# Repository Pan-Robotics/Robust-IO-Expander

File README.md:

# Robust-IO-Expander

    1. Dual MCP23S17 ICs: Harness the power of two MCP23S17 16-Bit I/O Expander ICs – one dedicated for inputs, ensuring robust data acquisition, 
    and the other exclusively for outputs, enabling precise device control.
    
    2. Galvanic Isolation with Opto Switches: Prioritize safety in your projects. Our I/O Expansion Module integrates opto switches for galvanic isolation, 
    shielding your electronics from voltage spikes and surges, ensuring secure and reliable operation.
    
    3. SPI Interface: Interact effortlessly with your system via the SPI interface. This streamlined communication protocol ensures swift and efficient data exchange, 
    allowing you to focus on the heart of your project.
    
    4. Connector Options: Tailor the module to your needs. Choose between 2.54mm header connectors for easy integration into your existing setups or Push terminals for a robust, secure connection. 
    The choice is yours, ensuring seamless compatibility with your specific project requirements.
    
    5. Effortless Expansion: Need more I/O pins? No problem! Our module is stackable, facilitating seamless expansion. 
    Connect multiple modules effortlessly to scale your projects without limitations, providing endless opportunities for your creative endeavors.
    
    6. Unparalleled Flexibility: Whether you're orchestrating automation systems, developing cutting-edge robotics, or creating interactive art installations, 
    the versatility of our I/O Expansion Module amplifies your creativity. Control motors, sensors, LEDs, and various devices effortlessly, opening doors to innovative projects.

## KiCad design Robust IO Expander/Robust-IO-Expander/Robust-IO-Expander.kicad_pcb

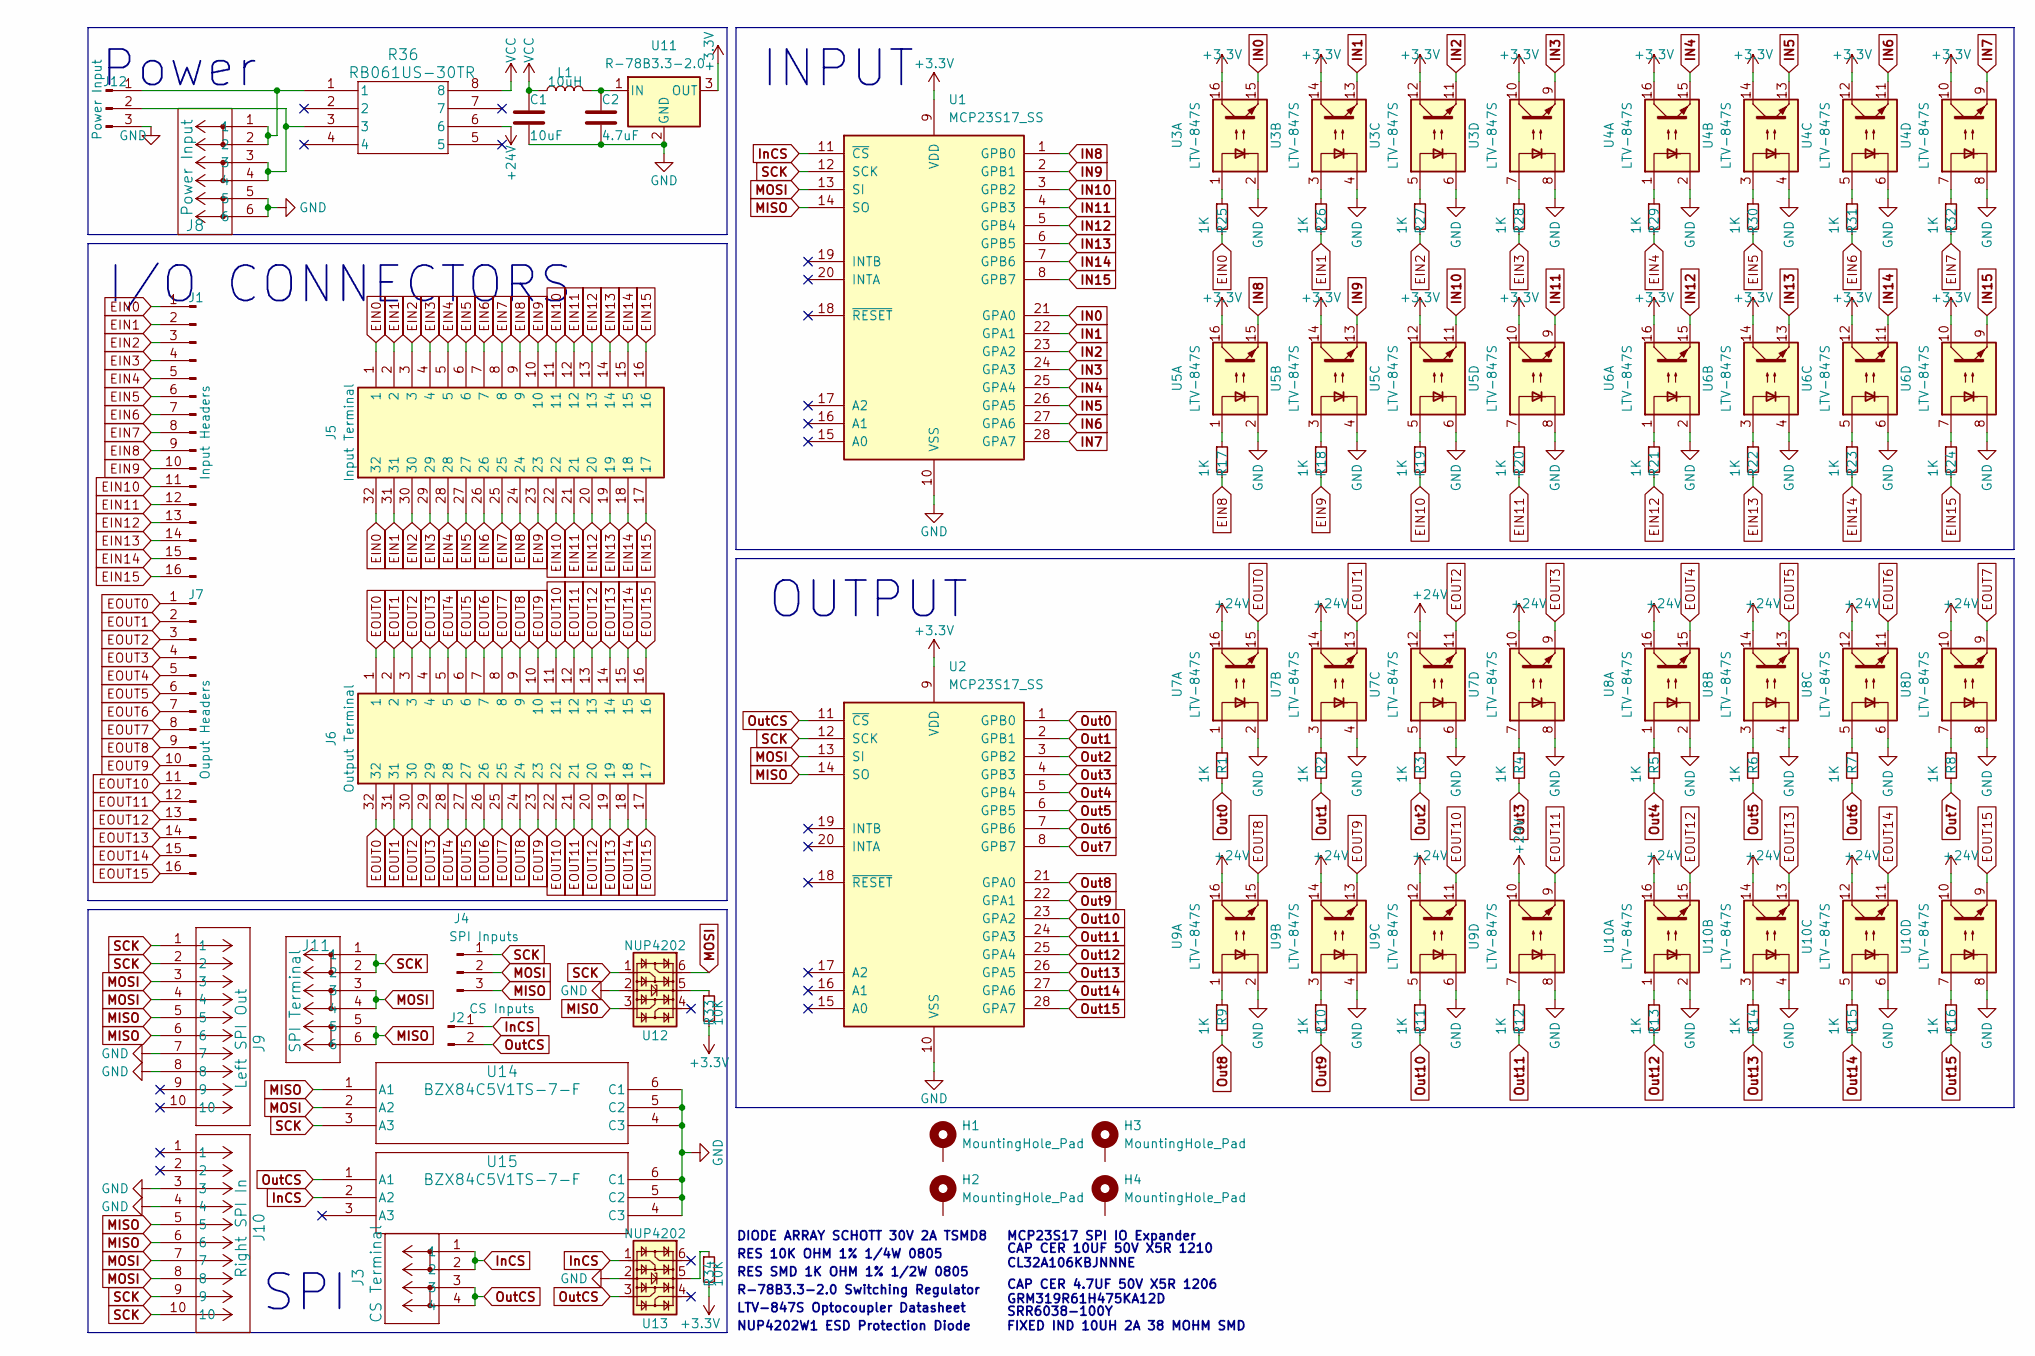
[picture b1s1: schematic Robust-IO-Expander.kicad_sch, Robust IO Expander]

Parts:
C1: 10uF; C_1210_3225Metric_Pad1.33x2.70mm_HandSolder
C2: 4.7uF; C_1206_3216Metric_Pad1.33x1.80mm_HandSolder
H1, H2, H3, H4: MountingHole_Pad; MountingHole_2.7mm_M2.5_ISO7380_Pad
J1: Input Headers; PinSocket_1x16_P2.54mm_Vertical
J2: CS Inputs; PinSocket_1x02_P2.54mm_Vertical
J3: CS Terminal; CONN_1862042
J4: SPI Inputs; PinSocket_1x03_P2.54mm_Vertical
J5: Input Terminal; 1862262; Mouser Part Number 651-1862262
J6: Output Terminal; 1862262; Mouser Part Number 651-1862262
J7: Ouput Headers; PinSocket_1x16_P2.54mm_Vertical
J8: Power Input; CONN_1862055
J9: Left SPI Out; CONN_LS2-105-01-X-D-RA1_SAI
J10: Right SPI In; CONN_LS2-105-01-X-D-RA2_SAI
J11: SPI Terminal; CONN_1862055
J12: Power Input; PinSocket_1x03_P2.54mm_Vertical
L1: 10uH; IND_BOURNS_SRR6038
R1, R2, R3, R4, R5, R6, R7, R8, R9, R10, R11, R12, R13, R14, R15, R16, R17, R18, R19, R20, R21, R22, R23, R24, R25, R26, R27, R28, R29, R30, R31, R32: 1K; R_0805_2012Metric_Pad1.20x1.40mm_HandSolder
R33, R34: 10K; R_0805_2012Metric_Pad1.20x1.40mm_HandSolder
R36: RB061US-30TR; DIO_RB061U_ROM
U1, U2: MCP23S17_SS; SSOP-28_5.3x10.2mm_P0.65mm
U3, U4, U5, U6, U7, U8, U9, U10: LTV-847S; SMDIP-16_W9.53mm
U11: R-78B3.3-2.0; Converter_DCDC_RECOM_R-78B-2.0_THT
U12, U13: NUP4202; SOT-363_SC-70-6
U14, U15: BZX84C5V1TS-7-F; SOT-363_DIO

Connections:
+3.3V: R33.2, R34.2, U1.9 (VDD), U2.9 (VDD), U3.10, U3.12, U3.14, U3.16, U4.10, U4.12, U4.14, U4.16, U5.10, U5.12, U5.14, U5.16, U6.10, U6.12, U6.14, U6.16, U11.3 (OUT)
+24V: R36.6, U7.10, U7.12, U7.14, U7.16, U8.10, U8.12, U8.14, U8.16, U9.10, U9.12, U9.14, U9.16, U10.10, U10.12, U10.14, U10.16
EIN0: J1.1, J5.1, J5.32, R25.2
EIN1: J1.2, J5.2, J5.31, R26.2
EIN2: J1.3, J5.3, J5.30, R27.2
EIN3: J1.4, J5.4, J5.29, R28.2
EIN4: J1.5, J5.5, J5.28, R29.2
EIN5: J1.6, J5.6, J5.27, R30.2
EIN6: J1.7, J5.7, J5.26, R31.2
EIN7: J1.8, J5.8, J5.25, R32.2
EIN8: J1.9, J5.9, J5.24, R17.2
EIN9: J1.10, J5.10, J5.23, R18.2
EIN10: J1.11, J5.11, J5.22, R19.2
EIN11: J1.12, J5.12, J5.21, R20.2
EIN12: J1.13, J5.13, J5.20, R21.2
EIN13: J1.14, J5.14, J5.19, R22.2
EIN14: J1.15, J5.15, J5.18, R23.2
EIN15: J1.16, J5.16, J5.17, R24.2
EOUT0: J6.1, J6.32, J7.1, U7.15
EOUT1: J6.2, J6.31, J7.2, U7.13
EOUT2: J6.3, J6.30, J7.3, U7.11
EOUT3: J6.4, J6.29, J7.4, U7.9
EOUT4: J6.5, J6.28, J7.5, U8.15
EOUT5: J6.6, J6.27, J7.6, U8.13
EOUT6: J6.7, J6.26, J7.7, U8.11
EOUT7: J6.8, J6.25, J7.8, U8.9
EOUT8: J6.9, J6.24, J7.9, U9.15
EOUT9: J6.10, J6.23, J7.10, U9.13
EOUT10: J6.11, J6.22, J7.11, U9.11
EOUT11: J6.12, J6.21, J7.12, U9.9
EOUT12: J6.13, J6.20, J7.13, U10.15
EOUT13: J6.14, J6.19, J7.14, U10.13
EOUT14: J6.15, J6.18, J7.15, U10.11
EOUT15: J6.16, J6.17, J7.16, U10.9
GND: C1.2, C2.2, J8.5, J8.6, J9.7, J9.8, J10.3, J10.4, J12.3, U1.10 (VSS), U2.10 (VSS), U3.2, U3.4, U3.6, U3.8, U4.2, U4.4, U4.6, U4.8, U5.2, U5.4, U5.6, U5.8, U6.2, U6.4, U6.6, U6.8, U7.2, U7.4, U7.6, U7.8, U8.2, U8.4, U8.6, U8.8, U9.2, U9.4, U9.6, U9.8, U10.2, U10.4, U10.6, U10.8, U11.2 (GND), U12.2, U13.2, U14.4 (C3), U14.5 (C2), U14.6 (C1), U15.4 (C3), U15.5 (C2), U15.6 (C1)
IN0: U1.21 (GPA0), U3.15
IN1: U1.22 (GPA1), U3.13
IN2: U1.23 (GPA2), U3.11
IN3: U1.24 (GPA3), U3.9
IN4: U1.25 (GPA4), U4.15
IN5: U1.26 (GPA5), U4.13
IN6: U1.27 (GPA6), U4.11
IN7: U1.28 (GPA7), U4.9
IN8: U1.1 (GPB0), U5.15
IN9: U1.2 (GPB1), U5.13
IN10: U1.3 (GPB2), U5.11
IN11: U1.4 (GPB3), U5.9
IN12: U1.5 (GPB4), U6.15
IN13: U1.6 (GPB5), U6.13
IN14: U1.7 (GPB6), U6.11
IN15: U1.8 (GPB7), U6.9
InCS: J2.1, J3.1, J3.2, U1.11 (~CS), U13.1, U15.2 (A2)
MISO: J4.3, J9.5, J9.6, J10.5, J10.6, J11.5, J11.6, U1.14 (SO), U2.14 (SO), U12.3, U14.1 (A1)
MOSI: J4.2, J9.3, J9.4, J10.7, J10.8, J11.3, J11.4, U1.13 (SI), U2.13 (SI), U12.6, U14.2 (A2)
unnamed: J8.1, J8.2, J12.1, R36.1
unnamed: J8.3, J8.4, J12.2, R36.3
unnamed: R1.1, U7.1
unnamed: R2.1, U7.3
unnamed: R3.1, U7.5
unnamed: R4.1, U7.7
unnamed: R5.1, U8.1
unnamed: R6.1, U8.3
unnamed: R7.1, U8.5
unnamed: R8.1, U8.7
unnamed: R9.1, U9.1
unnamed: R10.1, U9.3
unnamed: R11.1, U9.5
unnamed: R12.1, U9.7
unnamed: R13.1, U10.1
unnamed: R14.1, U10.3
unnamed: R15.1, U10.5
unnamed: R16.1, U10.7
unnamed: R17.1, U5.1
unnamed: R18.1, U5.3
unnamed: R19.1, U5.5
unnamed: R20.1, U5.7
unnamed: R21.1, U6.1
unnamed: R22.1, U6.3
unnamed: R23.1, U6.5
unnamed: R24.1, U6.7
unnamed: R25.1, U3.1
unnamed: R26.1, U3.3
unnamed: R27.1, U3.5
unnamed: R28.1, U3.7
unnamed: R29.1, U4.1
unnamed: R30.1, U4.3
unnamed: R31.1, U4.5
unnamed: R32.1, U4.7
unnamed: R33.1, U12.5
unnamed: R34.1, U13.5
unnamed: C2.1, L1.2, U11.1 (IN)
Out0: R1.2, U2.1 (GPB0)
Out1: R2.2, U2.2 (GPB1)
Out2: R3.2, U2.3 (GPB2)
Out3: R4.2, U2.4 (GPB3)
Out4: R5.2, U2.5 (GPB4)
Out5: R6.2, U2.6 (GPB5)
Out6: R7.2, U2.7 (GPB6)
Out7: R8.2, U2.8 (GPB7)
Out8: R9.2, U2.21 (GPA0)
Out9: R10.2, U2.22 (GPA1)
Out10: R11.2, U2.23 (GPA2)
Out11: R12.2, U2.24 (GPA3)
Out12: R13.2, U2.25 (GPA4)
Out13: R14.2, U2.26 (GPA5)
Out14: R15.2, U2.27 (GPA6)
Out15: R16.2, U2.28 (GPA7)
OutCS: J2.2, J3.3, J3.4, U2.11 (~CS), U13.3, U15.1 (A1)
SCK: J4.1, J9.1, J9.2, J10.9, J10.10, J11.1, J11.2, U1.12 (SCK), U2.12 (SCK), U12.1, U14.3 (A3)
VCC: C1.1, L1.1, R36.8

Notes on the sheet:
DIODE ARRAY SCHOTT 30V 2A TSMD8
RES SMD 1K OHM 1% 1/2W 0805
CAP CER 10UF 50V X5R 1210 CL32A106KBJNNNE
INPUT
NUP4202W1 ESD Protection Diode
SRR6038-100Y FIXED IND 10UH 2A 38 MOHM SMD
R-78B3.3-2.0 Switching Regulator
RES 10K OHM 1% 1/4W 0805
LTV-847S Optocoupler Datasheet
I/O CONNECTORS
CAP CER 4.7UF 50V X5R 1206 GRM319R61H475KA12D
OUTPUT
SPI
Power
MCP23S17 SPI IO Expander

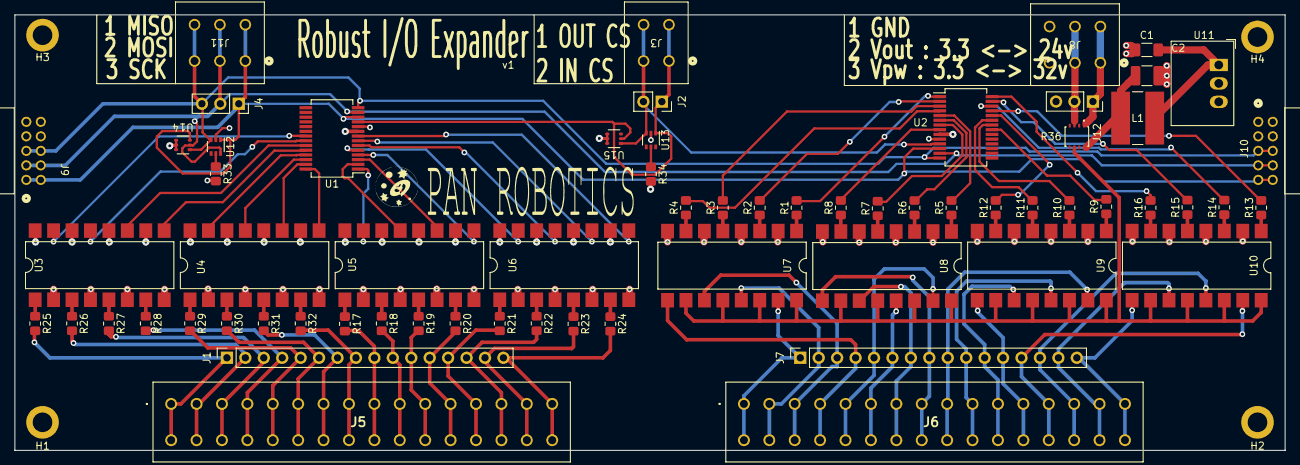
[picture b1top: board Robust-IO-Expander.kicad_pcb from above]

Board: 4 copper layers, 175.0 x 60.0 mm, 69 parts (0 on the bottom side), 110 nets.

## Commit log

2023-09-19 New Robust IO Expander Device
    AD 19/09/23: Schematic for Opto-isolated SPI IO Expander chip Added
2023-10-09 update
    AD 09/10/23
    finished schematic and all components on board
2023-10-15 Layout change
    AD 15/10/23: Add Screw terminals everywhere
    ESD Protection on IO and SPI Inputs
    3.3v Regulator for IO power
2023-12-10 Design Complete
    AD 10/12/23:
    Design Finalised
    BOM Created
    Gerber and POS Files Generate
2023-12-12 Updates
    AD 12/11/23
    1K Resistors inserted for 200R
    0603 components Error correct to 0805
    Post DFM Analysis Changes
2024-01-16 Clerical and Image Updates
